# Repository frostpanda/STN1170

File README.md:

<h2><b>Prototype of common OBD diagnostic board </b></h2>

Device uses STN1170 chip in QFTP package, form ScanTool company and it is compatible with ELM327, based on information, which can be found in datasheet about this integrated circuit. 

Main assumption about this prototype to be a modular to lower the cost of the device, because only 3 samples can be acquired through ScanTool company, so prototype has two boards. One with STN1170 and necessary components and second one with transceivers, which are required for communication with proper protocols and OBD chip, but also contains wireless and wired communication. 

Wireless communication was planned RN4870 BLE module. But because of bad implementation (???) or module was broken I can not force him to work properly. In the end it lost MAC address and this is common for modules, based on IS187x Bluetooth LE ICs and the main reason for it was as Microchip support claim “Inappropriate module reset”, but I didn’t get answer for my question, when I asked about, how this module should be reset, to prevent such behavior in the future. Finally I decided for HM-13 module. Module is already implemented and I need to do more tweaking in revision 2 to push next revision. For now module is working on revision 1 prototype board.

Wired communication with PC uses CP2102N UART to Bridge ICs. His cost is lower than FTDI chips and has a lot possible ways to configure it, beginning from drivers, ending at ICs, but soldering it without hot air station is not easy task to do, but it can be done with some patience.

After success of 1st prototype (working!), second was made. On the 2nd prototype everything was moved to the one 2 layers PCB board, with dimension of 4cm x 6cm (I will try to make it even smaller!, but I am concern about EMC problem with it and this could require use 4 layer PCB). Some of components are on the bottom side of the board. 

Checked protocols:
- [x] High Speed CAN
- [x] Medium Speed CAN 
- [x] Single Wire CAN 
- [x] K-LINE
- [x] L-LINE
- [ ] VPW 
- [ ] PWM

Basic connection tested with:
- Fiat Punto MK2 1.2 8V (MultiEcuScan)
- Opel Vectra C 1.8 16V 122KM 
- Citroen DS4 
- Mazda 3 BK 1.6 105KM Z6 2008 (ForScan)

Gallery: https://imgur.com/a/UtiDV

Video: https://youtu.be/GFeOGx49xKc

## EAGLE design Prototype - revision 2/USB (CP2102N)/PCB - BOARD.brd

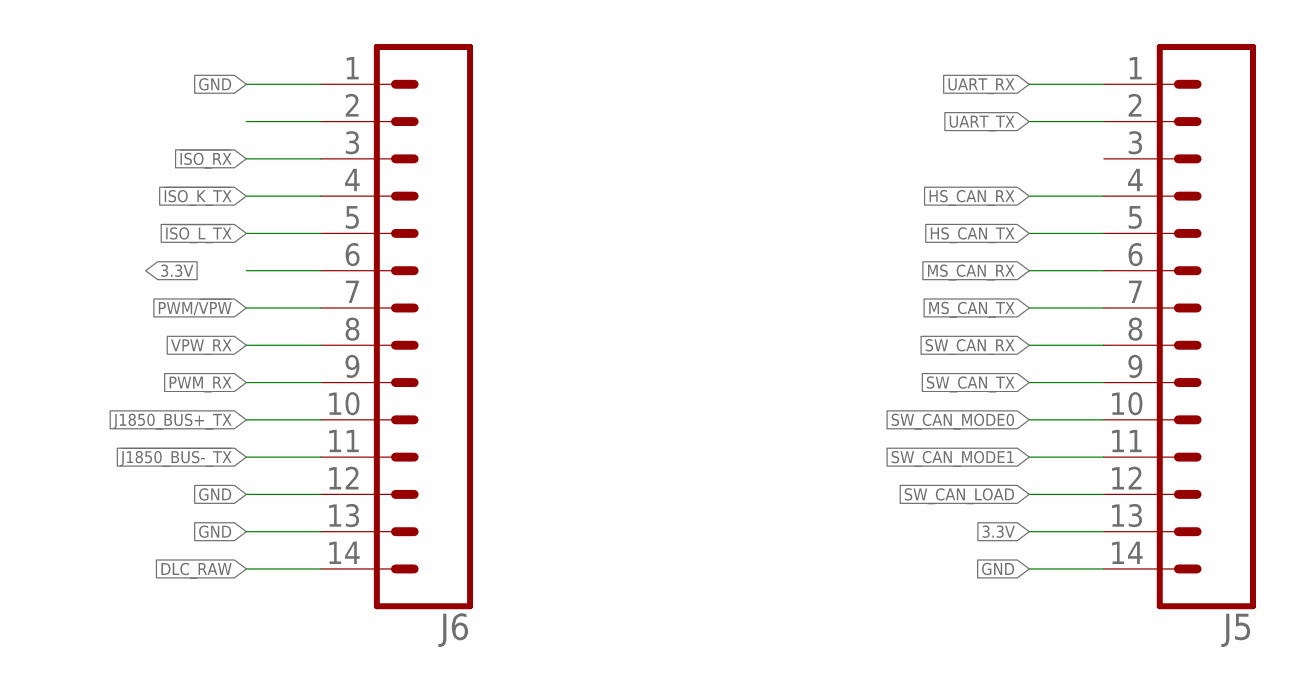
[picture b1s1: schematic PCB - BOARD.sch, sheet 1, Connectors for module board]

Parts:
J5, J6: CONN_14; 1X14

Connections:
3.3V: J5.13, J6.6; also elsewhere on the board
!ISO_K_TX: J6.4; also elsewhere on the board
!ISO_L_TX: J6.5; also elsewhere on the board
!ISO_RX: J6.3; also elsewhere on the board
!J1850_BUS-_TX: J6.11; also elsewhere on the board
DLC_RAW: J6.14; also elsewhere on the board
GND: J5.14, J6.1, J6.2, J6.12, J6.13; also elsewhere on the board
HS_CAN_RX: J5.4; also elsewhere on the board
HS_CAN_TX: J5.5; also elsewhere on the board
J1850_BUS+_TX: J6.10; also elsewhere on the board
MS_CAN_RX: J5.6; also elsewhere on the board
MS_CAN_TX: J5.7; also elsewhere on the board
PWM/!VPW: J6.7; also elsewhere on the board
PWM_RX: J6.9; also elsewhere on the board
SW_CAN_LOAD: J5.12; also elsewhere on the board
SW_CAN_MODE0: J5.10; also elsewhere on the board
SW_CAN_MODE1: J5.11; also elsewhere on the board
SW_CAN_RX: J5.8; also elsewhere on the board
SW_CAN_TX: J5.9; also elsewhere on the board
UART_RX: J5.1; also elsewhere on the board
UART_TX: J5.2; also elsewhere on the board
VPW_RX: J6.8; also elsewhere on the board

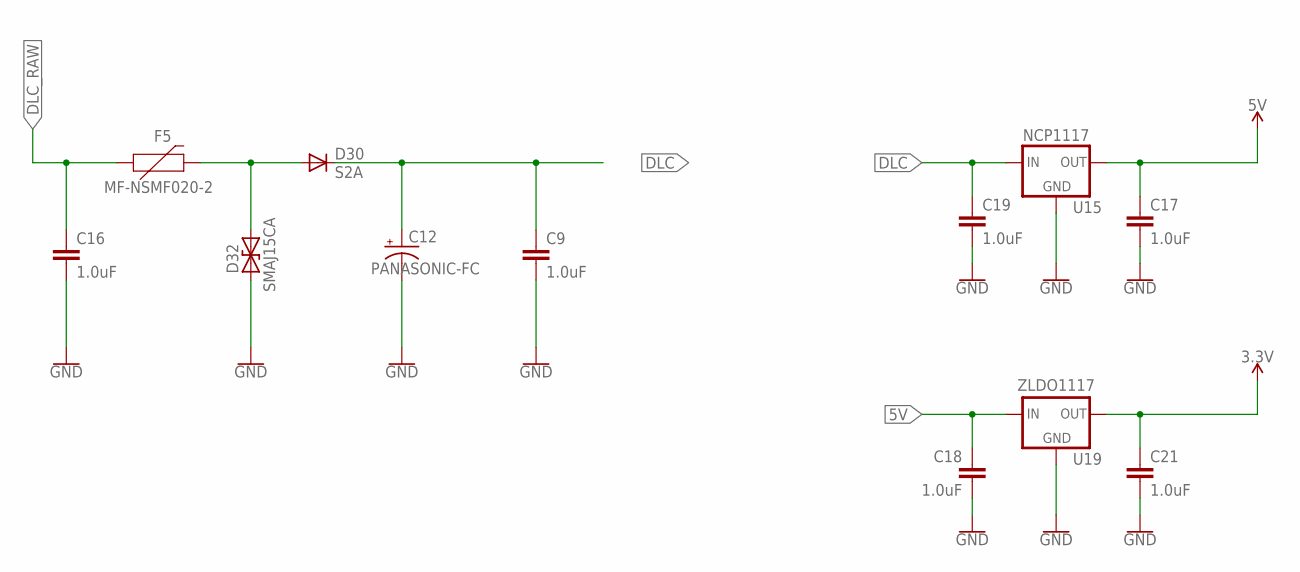
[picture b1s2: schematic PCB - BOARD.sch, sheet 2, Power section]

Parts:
C9, C16, C17, C18, C19, C21: 1.0uF; 0805
C12: PANASONIC-FC; 5X11
D30: S2A; DO214AA
D32: SMAJ15CA; DO214AC
F5: MF-NSMF020-2; 1206
U15: NCP1117; TO-252
U19: ZLDO1117; SOT223

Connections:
3.3V: C21.1, U19.2 (OUT), U19.4 (OUT); also elsewhere on the board
5V: C17.1, C18.1, U15.2 (OUT), U19.3 (IN); also elsewhere on the board
DLC: C9.1, C12.2 (+), C19.1, D30.C, U15.3 (IN); also elsewhere on the board
DLC_RAW: C16.1, F5.1; also elsewhere on the board
DLC_RAW2: D30.A, D32.C (2), F5.2
GND: C9.2, C12.1 (-), C16.2, C17.2, C18.2, C19.2, C21.2, D32.A (1), U15.1 (GND), U19.1 (GND); also elsewhere on the board

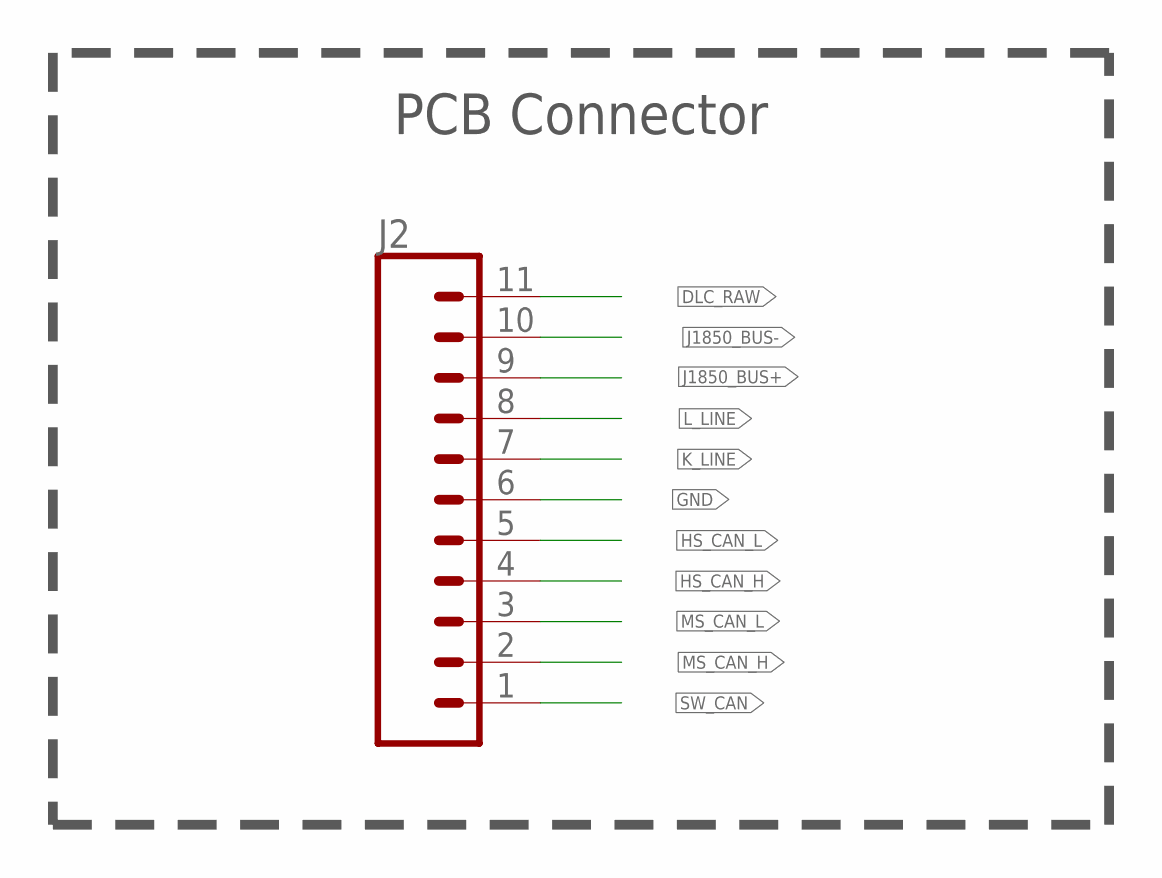
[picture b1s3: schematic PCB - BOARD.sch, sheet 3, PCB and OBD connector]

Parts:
J2: CONN_11; 1X11

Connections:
DLC_RAW: J2.11; also elsewhere on the board
GND: J2.6; also elsewhere on the board
HS_CAN_H: J2.4; also elsewhere on the board
HS_CAN_L: J2.5; also elsewhere on the board
J1850_BUS+: J2.9; also elsewhere on the board
J1850_BUS-: J2.10; also elsewhere on the board
K_LINE: J2.7; also elsewhere on the board
L_LINE: J2.8; also elsewhere on the board
MS_CAN_H: J2.2; also elsewhere on the board
MS_CAN_L: J2.3; also elsewhere on the board
SW_CAN: J2.1; also elsewhere on the board

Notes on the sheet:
PCB Connector

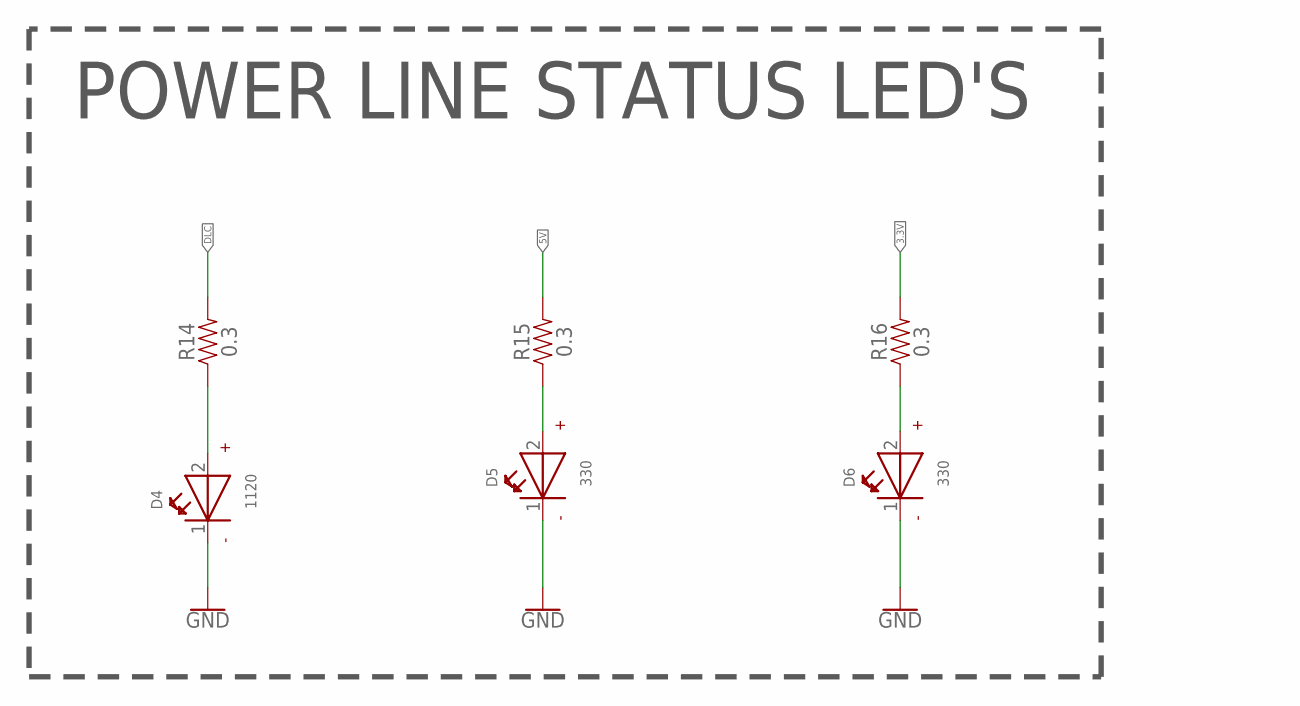
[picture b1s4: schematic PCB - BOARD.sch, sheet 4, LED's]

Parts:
D4: 1120; WL-SMCW_1206
D5, D6: 330; WL-SMCW_1206
R14, R15, R16: 0.3; 0805

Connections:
3.3V: R16.2; also elsewhere on the board
5V: R15.2; also elsewhere on the board
DLC: R14.2; also elsewhere on the board
GND: D4.1 (-), D5.1 (-), D6.1 (-); also elsewhere on the board
unnamed: D6.2 (+), R16.1
unnamed: D5.2 (+), R15.1
unnamed: D4.2 (+), R14.1

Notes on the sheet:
POWER LINE STATUS LED'S

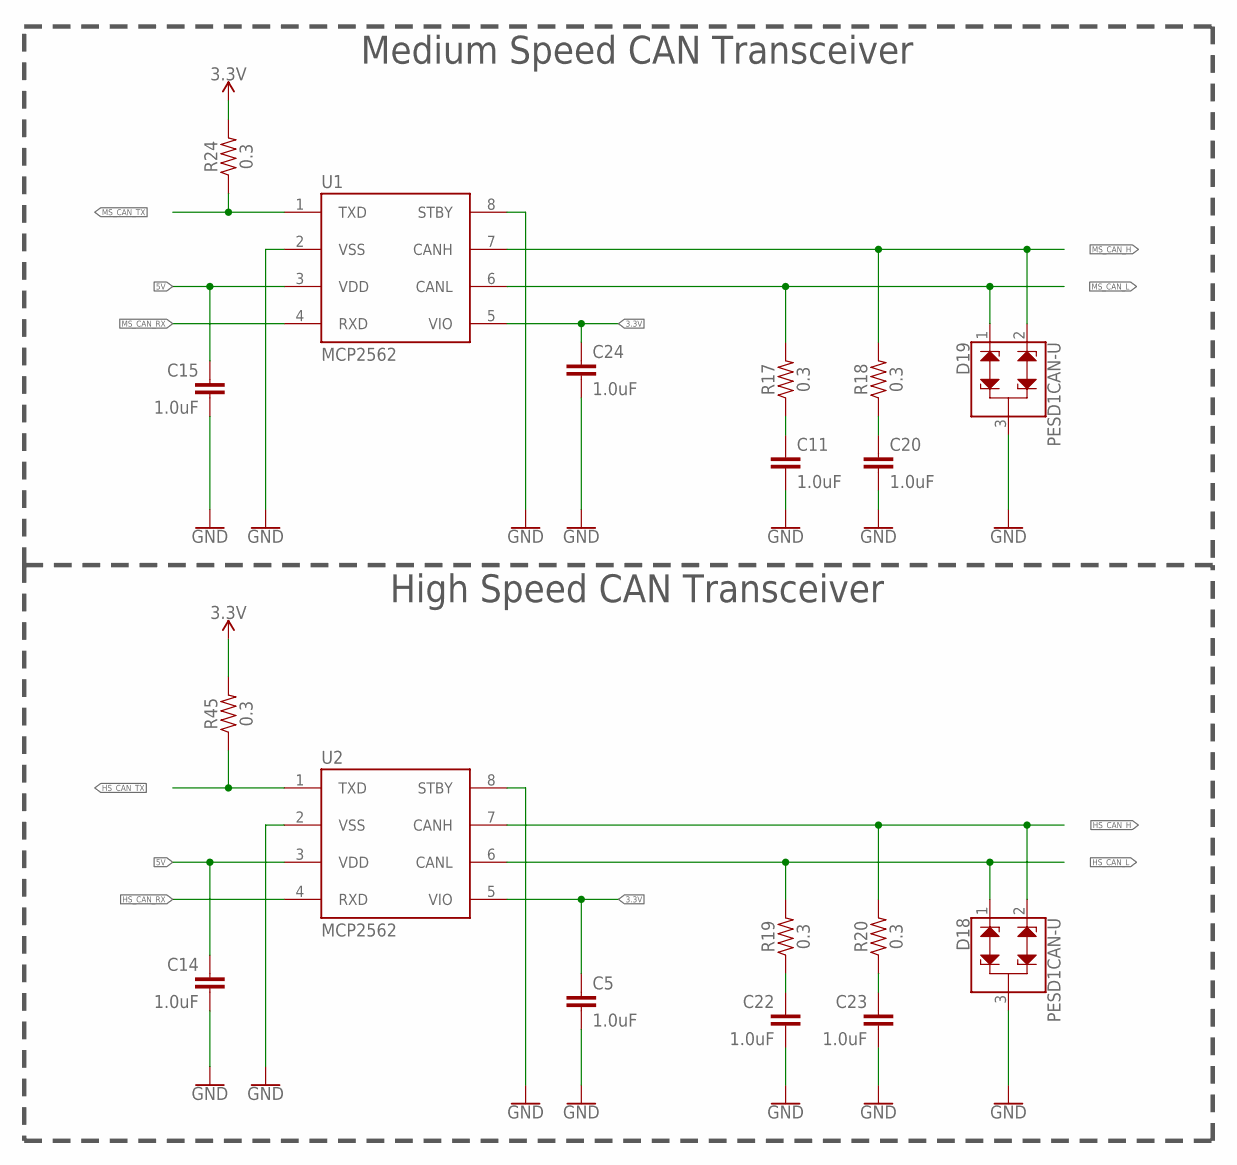
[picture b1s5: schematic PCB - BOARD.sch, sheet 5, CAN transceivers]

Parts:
C5, C11, C14, C15, C20, C22, C23, C24: 1.0uF; 0805
D18, D19: PESD1CAN-U; SOT323
R17, R18, R19, R20, R24, R45: 0.3; 0805
U1, U2: MCP2562; SOIC-8

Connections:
3.3V: C5.1, C24.1, R24.2, R45.2, U1.5 (VIO), U2.5 (VIO); also elsewhere on the board
5V: C14.1, C15.1, U1.3 (VDD), U2.3 (VDD); also elsewhere on the board
GND: C5.2, C11.2, C14.2, C15.2, C20.2, C22.2, C23.2, C24.2, D18.3, D19.3, U1.2 (VSS), U1.8 (STBY), U2.2 (VSS), U2.8 (STBY); also elsewhere on the board
HS_CAN_H: D18.2, R20.2, U2.7 (CANH); also elsewhere on the board
HS_CAN_L: D18.1, R19.2, U2.6 (CANL); also elsewhere on the board
HS_CAN_RX: U2.4 (RXD); also elsewhere on the board
HS_CAN_TX: R45.1, U2.1 (TXD); also elsewhere on the board
MS_CAN_H: D19.2, R18.2, U1.7 (CANH); also elsewhere on the board
MS_CAN_L: D19.1, R17.2, U1.6 (CANL); also elsewhere on the board
MS_CAN_RX: U1.4 (RXD); also elsewhere on the board
MS_CAN_TX: R24.1, U1.1 (TXD); also elsewhere on the board
unnamed: C11.1, R17.1
unnamed: C20.1, R18.1
unnamed: C22.1, R19.1
unnamed: C23.1, R20.1

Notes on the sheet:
Medium Speed CAN Transceiver
High Speed CAN Transceiver

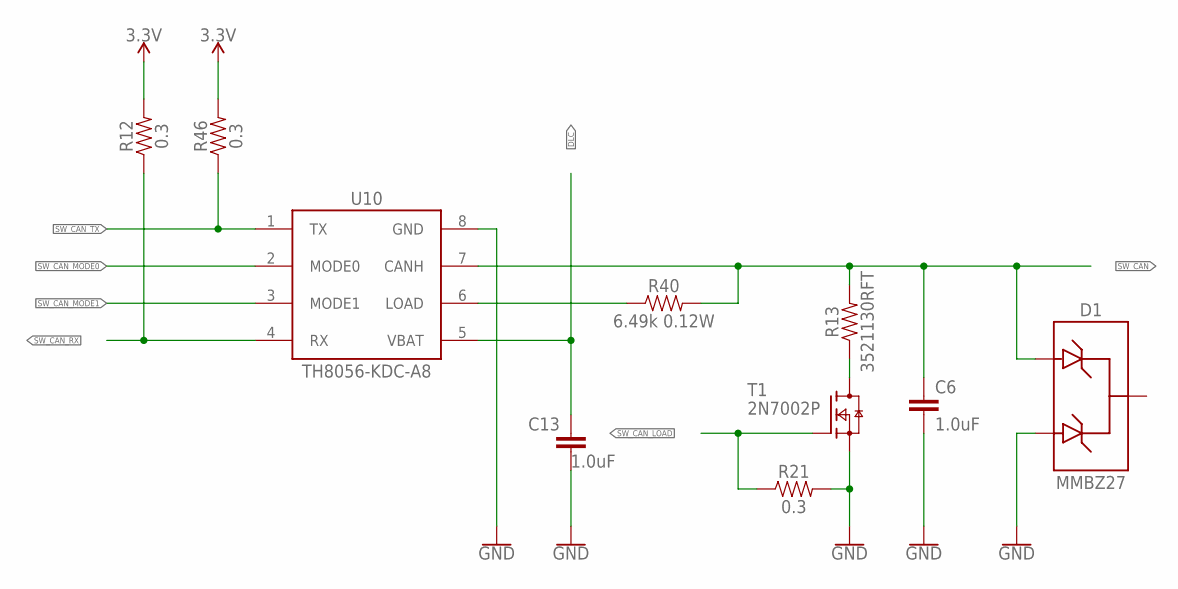
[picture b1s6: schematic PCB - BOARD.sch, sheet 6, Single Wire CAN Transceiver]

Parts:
C6, C13: 1.0uF; 0805
D1: MMBZ27; SOT23-3
R12, R21, R46: 0.3; 0805
R13: 3521130RFT; 3521
R40: 6.49k 0.12W; 1206
T1: 2N7002P; SOT23
U10: TH8056-KDC-A8; SOIC-8

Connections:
3.3V: R12.2, R46.2; also elsewhere on the board
DLC: C13.1, U10.5 (VBAT); also elsewhere on the board
GND: C6.2, C13.2, D1.2 (A2), R21.2, T1.2 (S), U10.8 (GND); also elsewhere on the board
LOAD: R40.1, U10.6 (LOAD)
unnamed: R13.1, T1.3 (D)
SW_CAN: C6.1, D1.1 (A1), R13.2, R40.2, U10.7 (CANH); also elsewhere on the board
SW_CAN_LOAD: R21.1, T1.1 (G); also elsewhere on the board
SW_CAN_MODE0: U10.2 (MODE0); also elsewhere on the board
SW_CAN_MODE1: U10.3 (MODE1); also elsewhere on the board
SW_CAN_RX: R12.1, U10.4 (RX); also elsewhere on the board
SW_CAN_TX: R46.1, U10.1 (TX); also elsewhere on the board

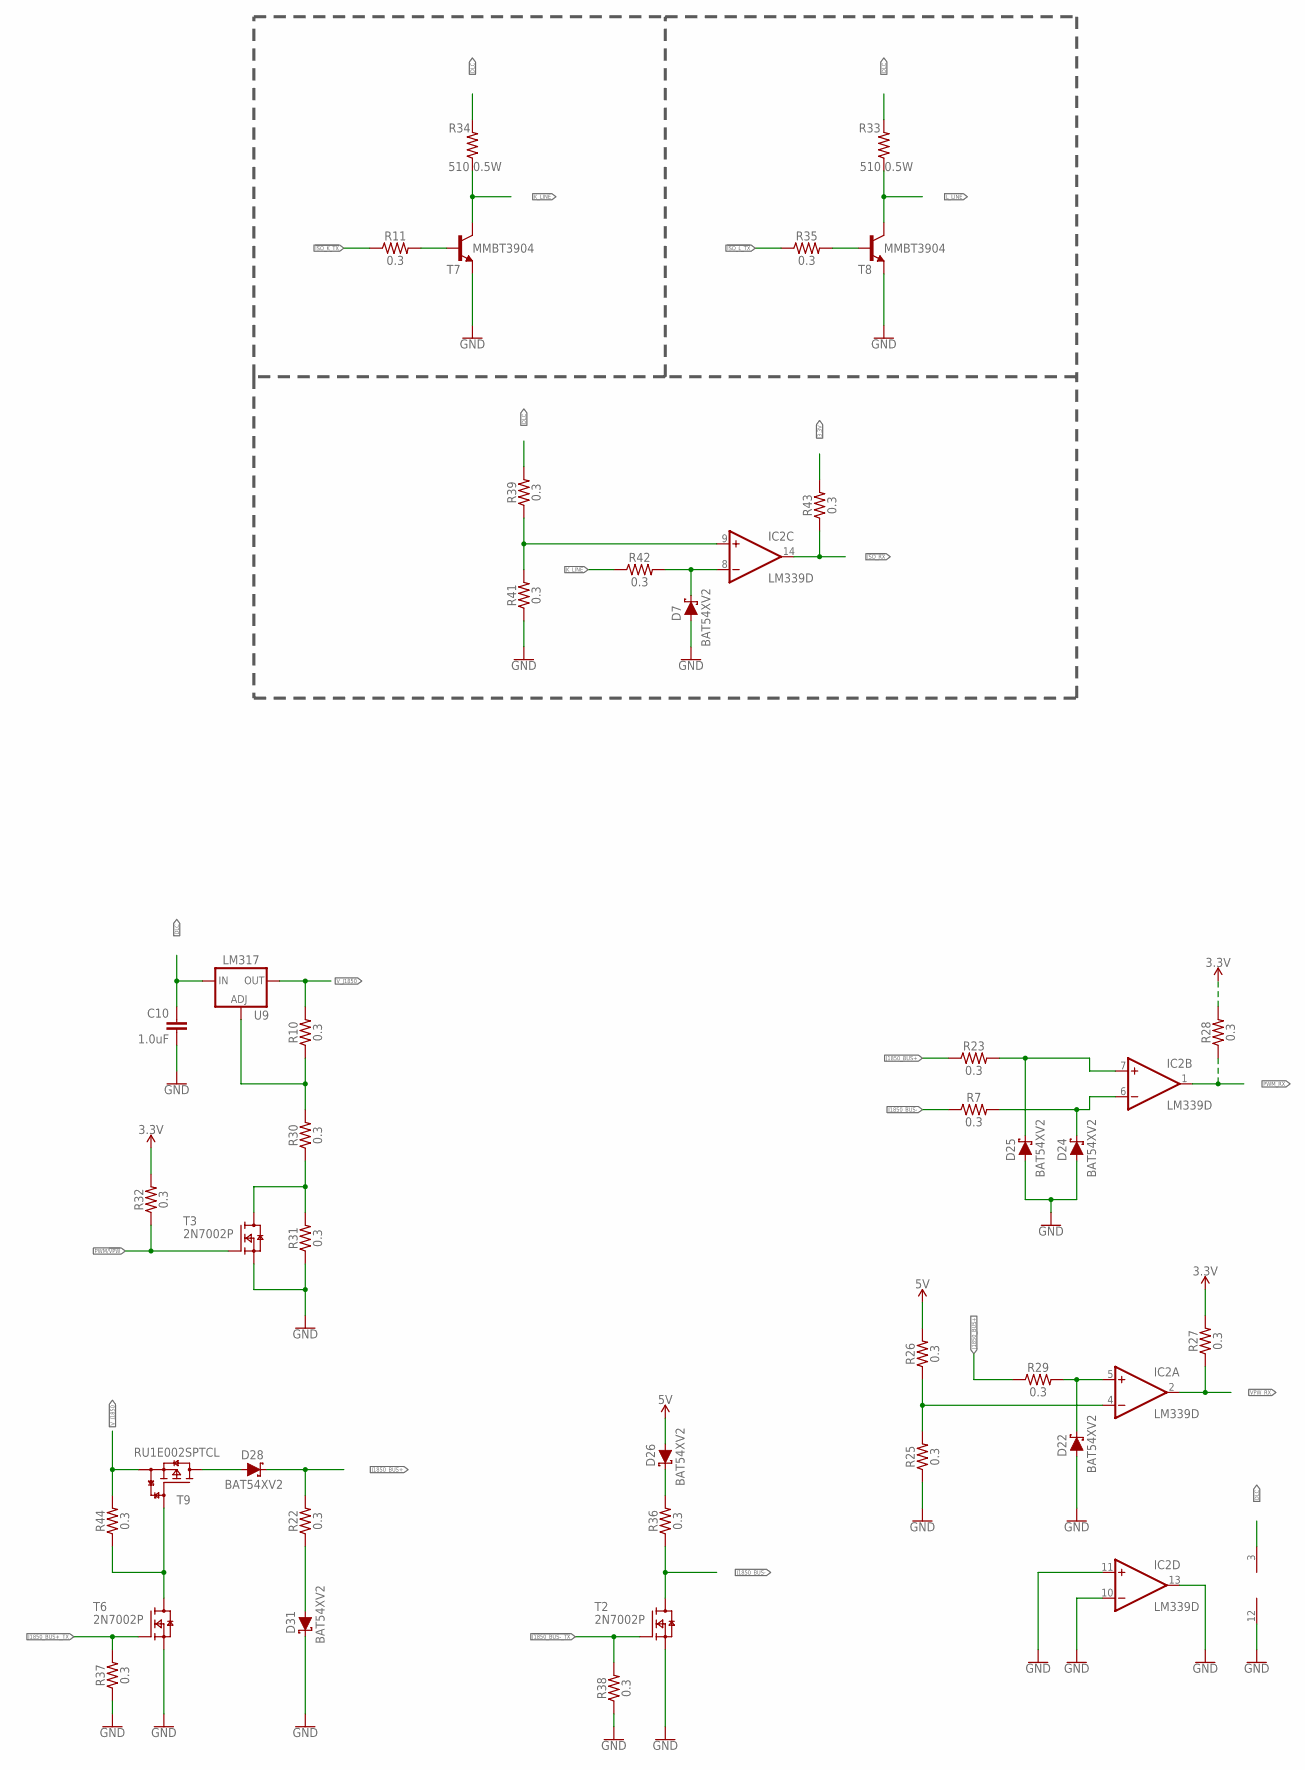
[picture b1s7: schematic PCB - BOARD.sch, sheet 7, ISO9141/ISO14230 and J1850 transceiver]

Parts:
C10: 1.0uF; 0805
D7, D22, D24, D25, D26, D28, D31: BAT54XV2; SOD-523F
IC2: LM339D; SO14
R7, R10, R11, R22, R23, R25, R26, R27, R28, R29, R30, R31, R32, R35, R36, R37, R38, R39, R41, R42, R43, R44: 0.3; 0805
R33, R34: 510 0.5W; 1210
T2, T3, T6: 2N7002P; SOT23
T7, T8: MMBT3904; SOT23-BEC
T9: RU1E002SPTCL; SOT323
U9: LM317; SOT223

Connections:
3.3V: R27.2, R28.2, R32.2, R43.2; also elsewhere on the board
5V: D26.A, R26.2; also elsewhere on the board
!ISO_K_TX: R11.1; also elsewhere on the board
!ISO_L_TX: R35.1; also elsewhere on the board
!ISO_RX: IC2.14 (OUT), R43.1; also elsewhere on the board
!J1850_BUS-_TX: R38.2, T2.1 (G); also elsewhere on the board
ADJ: R10.1, R30.2, U9.1 (ADJ)
COMPARATOR+: D22.C, IC2.5 (+IN), R29.2
COMPARATOR-: IC2.4 (-IN), R25.2, R26.1
DLC: C10.1, IC2.3 (V+), R33.2, R34.2, R39.2, U9.3 (IN); also elsewhere on the board
GND: C10.2, D7.A, D22.A, D24.A, D25.A, D31.C, IC2.10 (-IN), IC2.11 (+IN), IC2.12 (GND), IC2.13 (OUT), R25.1, R31.1, R37.1, R38.1, R41.1, T2.2 (S), T3.2 (S), T6.2 (S), T7.E, T8.E; also elsewhere on the board
J1850_BUS+: D25.C, D28.C, IC2.7 (+IN), R22.2, R23.1, R23.2, R29.1; also elsewhere on the board
J1850_BUS+_TX: R37.2, T6.1 (G); also elsewhere on the board
J1850_BUS-: D24.C, IC2.6 (-IN), R7.1, R7.2, R36.1, T2.3 (D); also elsewhere on the board
K-LINE: D7.C, IC2.8 (-IN), R42.2
K_LINE: R34.1, R42.1, T7.C; also elsewhere on the board
L_LINE: R33.1, T8.C; also elsewhere on the board
unnamed: R44.1, T6.3 (D), T9.1 (G)
unnamed: D26.C, R36.2
unnamed: IC2.9 (+IN), R39.1, R41.2
unnamed: D28.A, T9.3 (D)
unnamed: D31.A, R22.1
unnamed: R35.2, T8.B
unnamed: R11.2, T7.B
unnamed: R30.1, R31.2, T3.3 (D)
PWM/!VPW: R32.1, T3.1 (G); also elsewhere on the board
PWM_RX: IC2.1 (OUT), R28.1; also elsewhere on the board
VPW_RX: IC2.2 (OUT), R27.1; also elsewhere on the board
V_J1850: R10.2, R44.2, T9.2 (S), U9.2 (OUT), U9.4 (OUT)

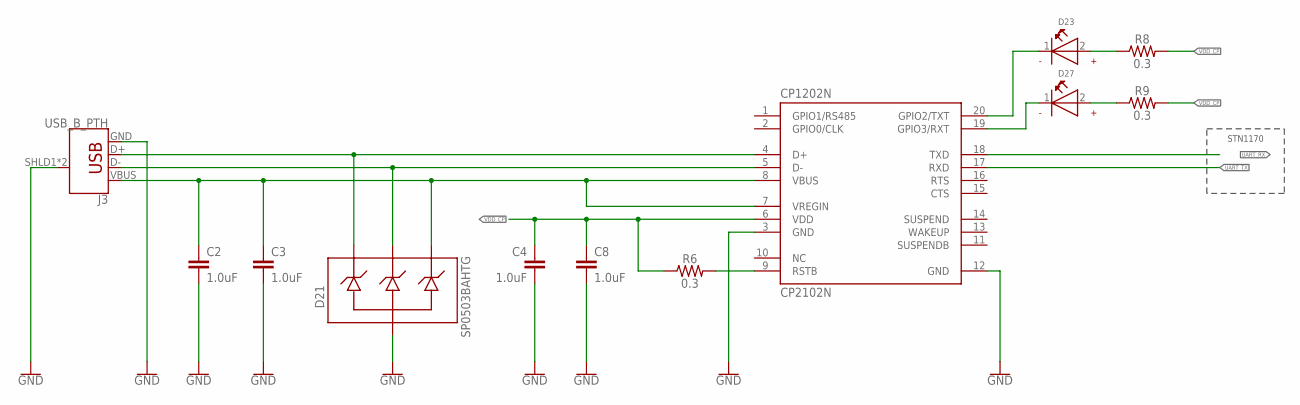
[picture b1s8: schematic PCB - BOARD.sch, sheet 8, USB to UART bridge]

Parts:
C2, C3, C4, C8: 1.0uF; 0805
CP1202N: CP2102N; QFN20
D21: SP0503BAHTG; SOT143-4
D23, D27: WL-SMCW-150120BS75000-B; WL-SMCW_1206
J3: USB_B_PTH; USB-B-PTH
R6, R8, R9: 0.3; 0805

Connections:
D+: CP1202N.4 (D+), D21.4, J3.D+
D-: CP1202N.5 (D-), D21.3, J3.D-
GND: C2.2, C3.2, C4.2, C8.2, CP1202N.3 (GND), CP1202N.12 (GND), D21.1, J3.GND, J3.SHLD1 (SHIELD), J3.SHLD2 (SHIELD); also elsewhere on the board
unnamed: CP1202N.9 (RSTB), R6.2
unnamed: CP1202N.20 (GPIO2/TXT), D23.1 (-)
unnamed: CP1202N.19 (GPIO3/RXT), D27.1 (-)
unnamed: D23.2 (+), R8.1
unnamed: D27.2 (+), R9.1
UART_RX: CP1202N.18 (TXD); also elsewhere on the board
UART_TX: CP1202N.17 (RXD); also elsewhere on the board
VBUS: C2.1, C3.1, CP1202N.7 (VREGIN), CP1202N.8 (VBUS), D21.2, J3.VBUS
VDD_CP: C4.1, C8.1, CP1202N.6 (VDD), R6.1, R8.2, R9.2

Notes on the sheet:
STN1170

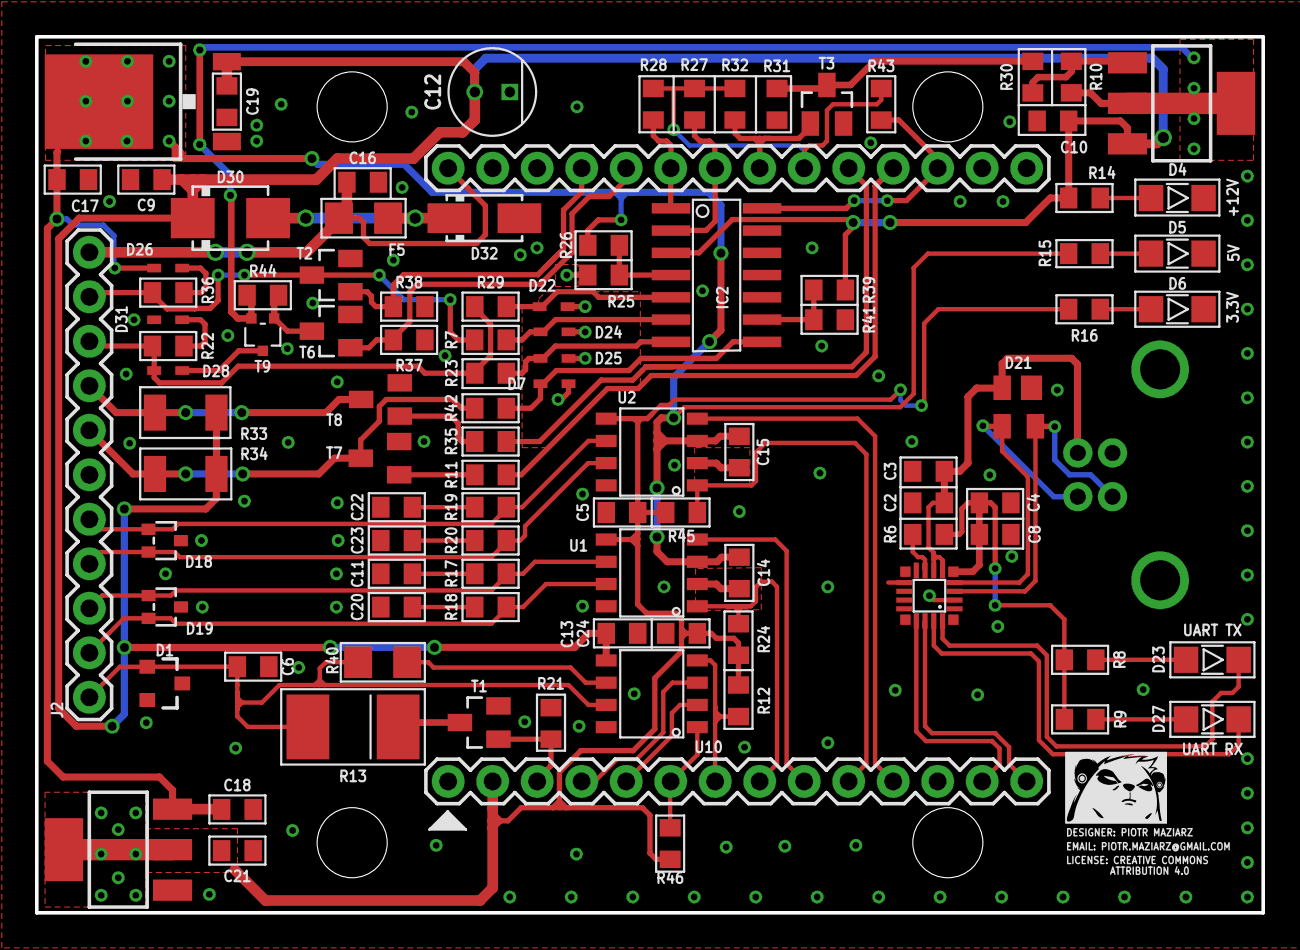
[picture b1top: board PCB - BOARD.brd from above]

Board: 2 copper layers, 70.0 x 50.0 mm, 103 parts (1 on the bottom side), 65 nets.

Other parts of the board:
U$1, U$2: LOGO2

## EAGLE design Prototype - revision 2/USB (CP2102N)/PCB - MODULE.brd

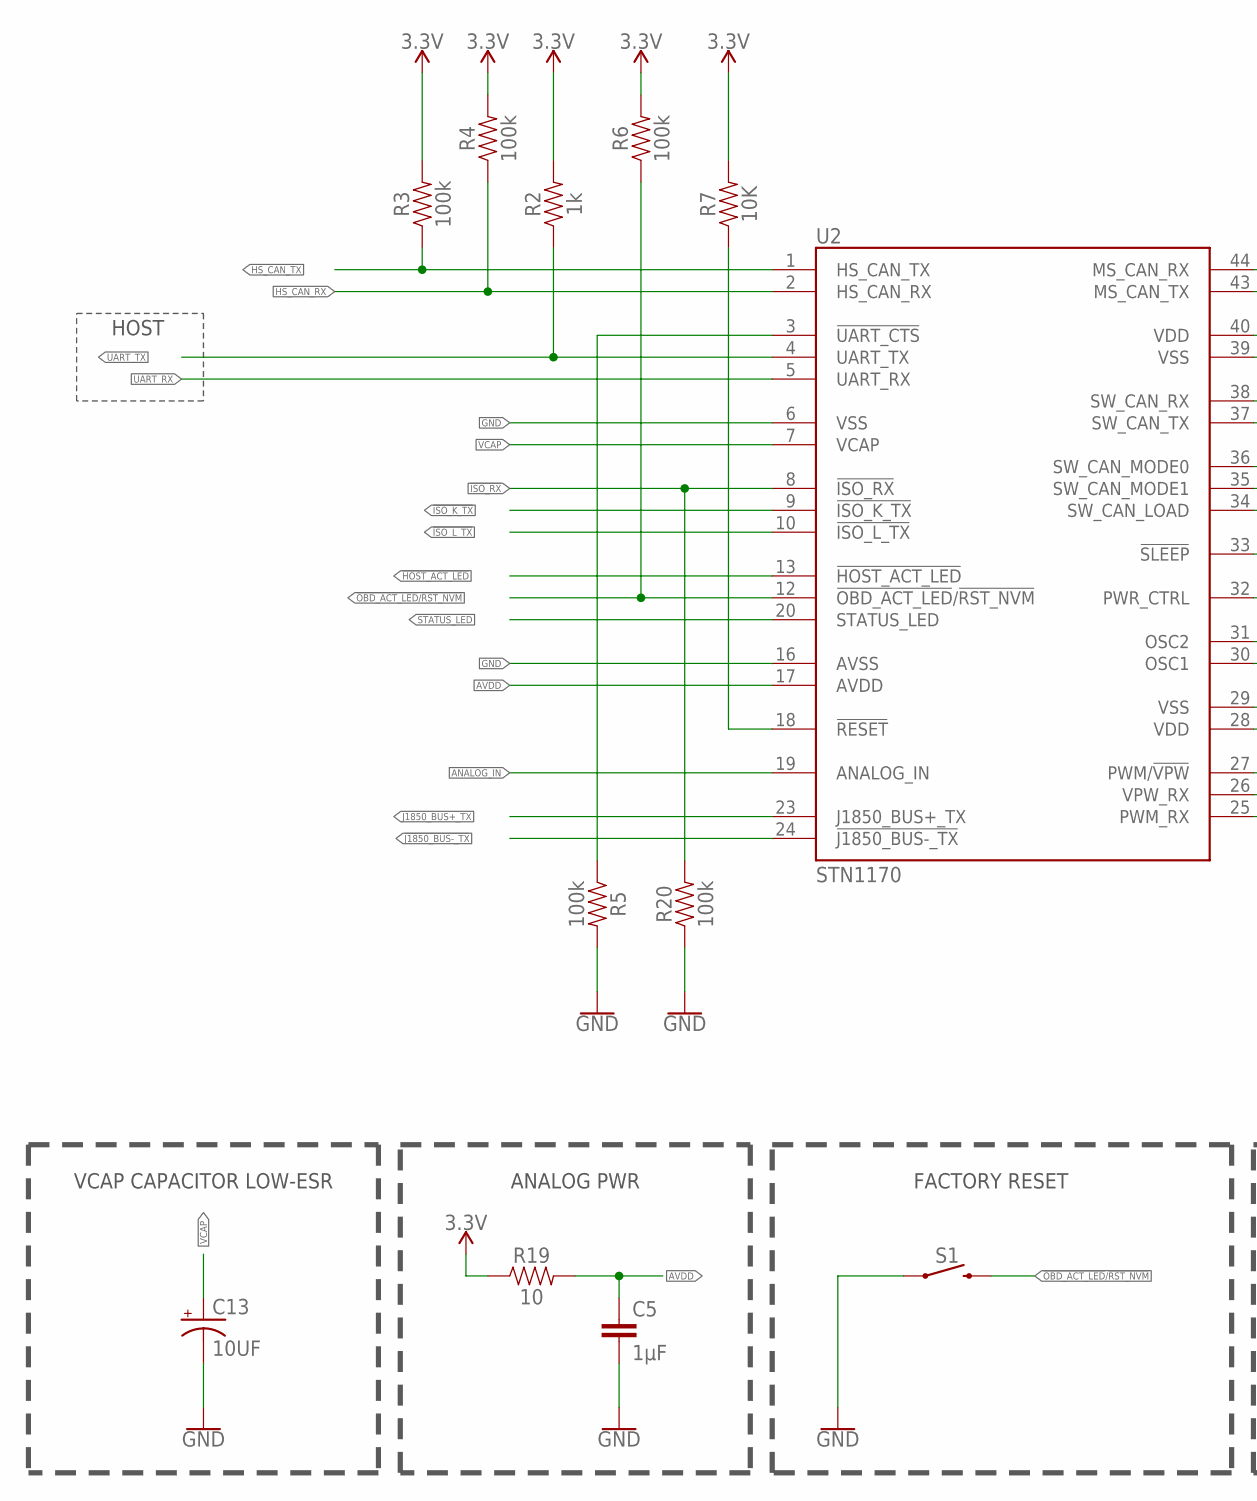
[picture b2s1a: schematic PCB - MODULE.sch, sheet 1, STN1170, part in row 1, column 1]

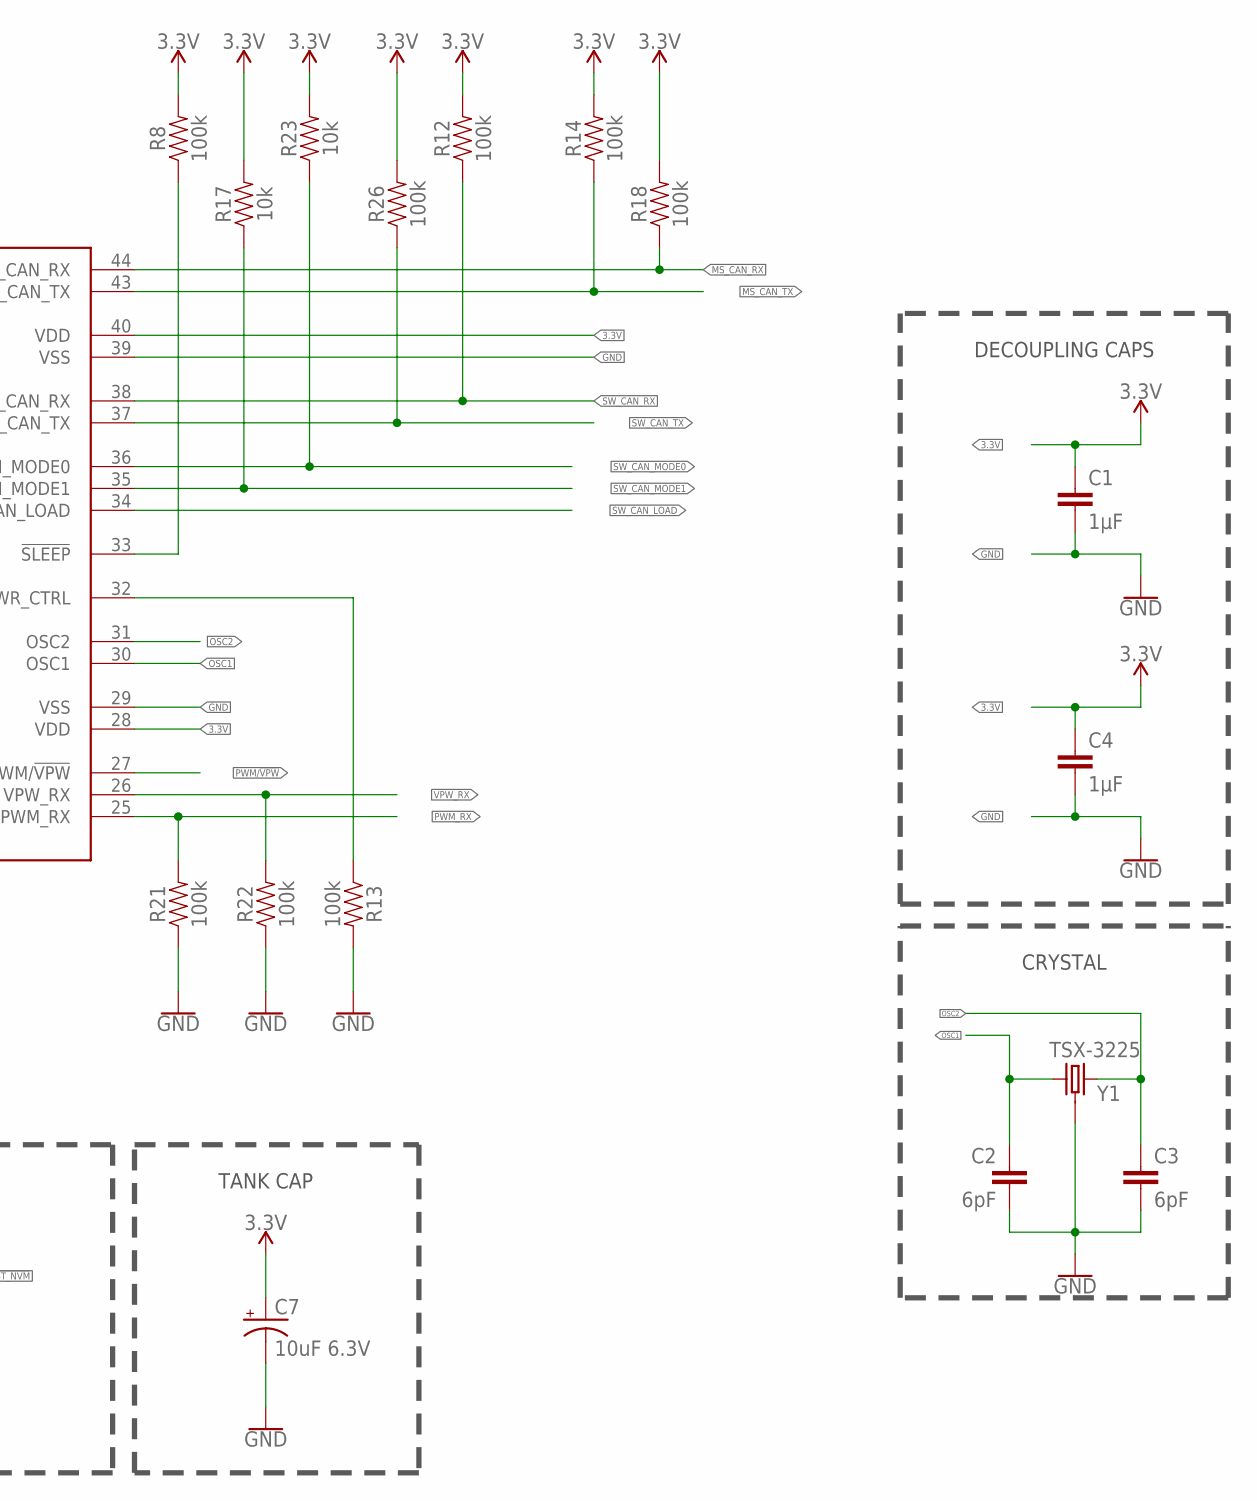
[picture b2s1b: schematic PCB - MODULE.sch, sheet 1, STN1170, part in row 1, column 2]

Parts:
C1, C4, C5: 1µF; 0805
C2, C3: 6pF; 0805
C7: 10uF 6.3V; EIA3216
C13: 10UF; 1206
R2: 1k; 0805
R3, R4, R5, R6, R8, R12, R13, R14, R18, R20, R21, R22, R26: 100k; 0805
R7: 10K; 0805
R17, R23: 10k; 0805
R19: 10; 0805
S1: B3U; B3U-WO-GT-WO-B
U2: STN1170; TQFP44
Y1: TSX-3225; TSX-3225-SOLDERING-IRON

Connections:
3.3V: C1.1, C4.1, C7.+, R2.2, R3.2, R4.2, R6.2, R7.2, R8.2, R12.2, R14.2, R17.2, R18.2, R19.1, R23.2, R26.2, U2.28 (VDD), U2.40 (VDD); also elsewhere on the board
!HOST_ACT_LED: U2.13 (!HOST_ACT_LED); also elsewhere on the board
!ISO_K_TX: U2.9 (!ISO_K_TX); also elsewhere on the board
!ISO_L_TX: U2.10 (!ISO_L_TX); also elsewhere on the board
!ISO_RX: R20.2, U2.8 (!ISO_RX); also elsewhere on the board
!J1850_BUS-_TX: U2.24 (!J1850_BUS-_TX); also elsewhere on the board
!OBD_ACT_LED!/!RST_NVM: R6.1, S1.2, U2.12 (!OBD_ACT_LED!/!RST_NVM); also elsewhere on the board
!RESET: R7.1, U2.18 (!RESET)
!SLEEP: R8.1, U2.33 (!SLEEP)
!UART_CTS: R5.1, U2.3 (!UART_CTS)
ANALOG_IN: U2.19 (ANALOG_IN); also elsewhere on the board
AVDD: C5.1, R19.2, U2.17 (AVDD)
GND: C1.2, C2.2, C3.2, C4.2, C5.2, C7.-, C13.2 (-), R5.2, R13.2, R20.1, R21.1, R22.1, S1.1, U2.6 (VSS), U2.16 (AVSS), U2.29 (VSS), U2.39 (VSS), Y1.2 (3), Y1.4 (3); also elsewhere on the board
HS_CAN_RX: R4.1, U2.2 (HS_CAN_RX); also elsewhere on the board
HS_CAN_TX: R3.1, U2.1 (HS_CAN_TX); also elsewhere on the board
J1850_BUS+_TX: U2.23 (J1850_BUS+_TX); also elsewhere on the board
MS_CAN_RX: R18.1, U2.44 (MS_CAN_RX); also elsewhere on the board
MS_CAN_TX: R14.1, U2.43 (MS_CAN_TX); also elsewhere on the board
OSC1: C2.1, U2.30 (OSC1), Y1.1
OSC2: C3.1, U2.31 (OSC2), Y1.3 (2)
PWM/!VPW: U2.27 (PWM/!VPW!); also elsewhere on the board
PWM_RX: R21.2, U2.25 (PWM_RX); also elsewhere on the board
PWR_CTRL: R13.1, U2.32 (PWR_CTRL)
STATUS_LED: U2.20 (STATUS_LED); also elsewhere on the board
SW_CAN_LOAD: U2.34 (SW_CAN_LOAD); also elsewhere on the board
SW_CAN_MODE0: R23.1, U2.36 (SW_CAN_MODE0); also elsewhere on the board
SW_CAN_MODE1: R17.1, U2.35 (SW_CAN_MODE1); also elsewhere on the board
SW_CAN_RX: R12.1, U2.38 (SW_CAN_RX); also elsewhere on the board
SW_CAN_TX: R26.1, U2.37 (SW_CAN_TX); also elsewhere on the board
UART_RX: U2.5 (UART_RX); also elsewhere on the board
UART_TX: R2.1, U2.4 (UART_TX); also elsewhere on the board
VCAP: C13.1 (+), U2.7 (VCAP)
VPW_RX: R22.2, U2.26 (VPW_RX); also elsewhere on the board

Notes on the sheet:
HOST
ANALOG PWR
CRYSTAL
VCAP CAPACITOR LOW-ESR
DECOUPLING CAPS
FACTORY RESET
TANK CAP

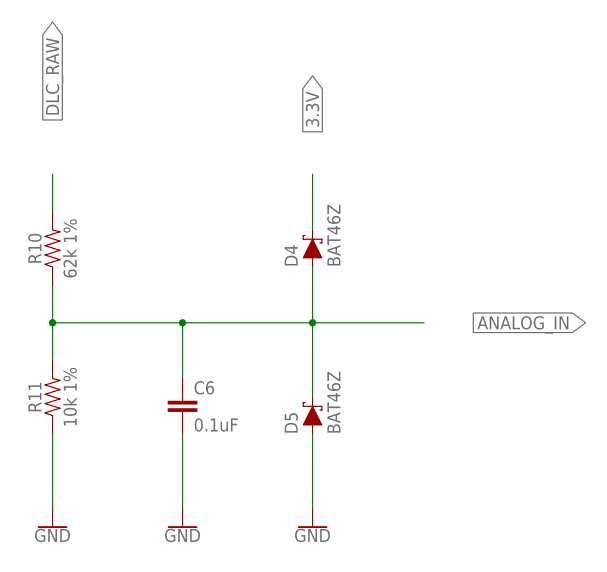
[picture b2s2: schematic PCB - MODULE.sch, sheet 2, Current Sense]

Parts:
C6: 0.1uF; 0805
D4, D5: BAT46Z; SOD-123
R10: 62k 1%; 0805
R11: 10k 1%; 0805

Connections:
3.3V: D4.C; also elsewhere on the board
ANALOG_IN: C6.1, D4.A, D5.C, R10.1, R11.2; also elsewhere on the board
DLC_RAW: R10.2; also elsewhere on the board
GND: C6.2, D5.A, R11.1; also elsewhere on the board

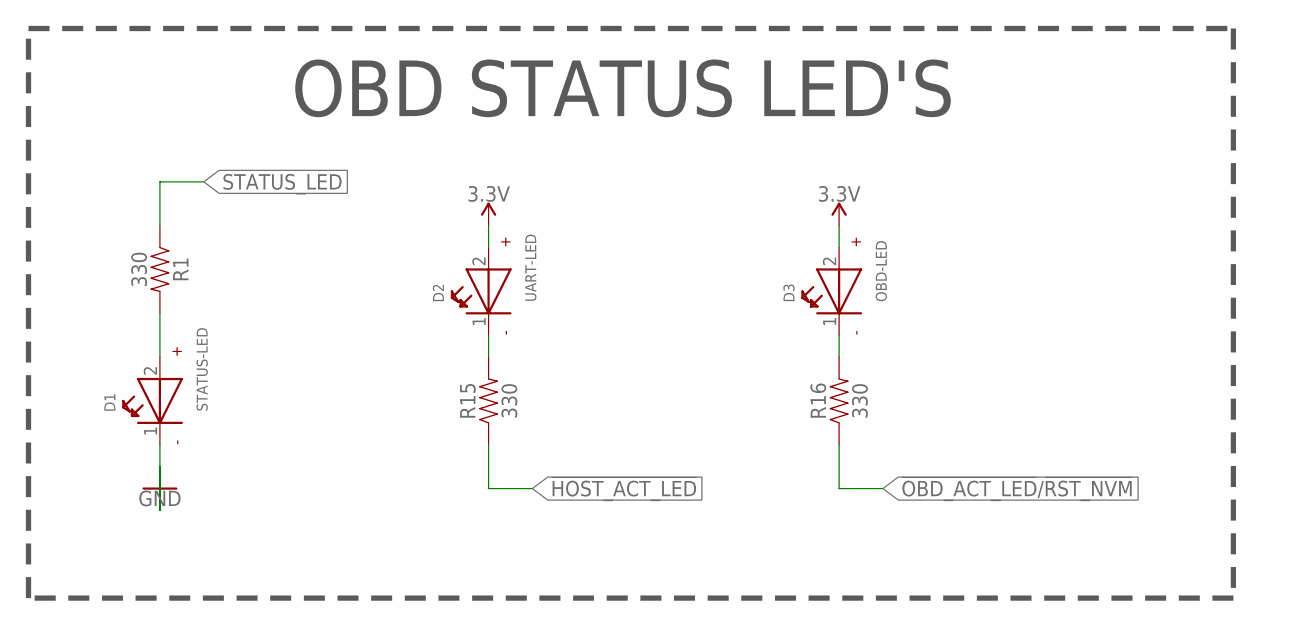
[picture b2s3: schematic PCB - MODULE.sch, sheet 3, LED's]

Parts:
D1: STATUS-LED; WL-SMCW_1206
D2: UART-LED; WL-SMCW_1206
D3: OBD-LED; WL-SMCW_1206
R1, R15, R16: 330; 0805

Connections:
3.3V: D2.2 (+), D3.2 (+); also elsewhere on the board
!HOST_ACT_LED: R15.1; also elsewhere on the board
!OBD_ACT_LED!/!RST_NVM: R16.1; also elsewhere on the board
GND: D1.1 (-); also elsewhere on the board
unnamed: D1.2 (+), R1.2
unnamed: D3.1 (-), R16.2
unnamed: D2.1 (-), R15.2
STATUS_LED: R1.1; also elsewhere on the board

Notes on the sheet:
OBD STATUS LED'S

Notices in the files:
Prototype - revision 2/USB (CP2102N)/PCB - BOARD.brd:
LICENSE: CREATIVE COMMONS
ATTRIBUTION 4.0
Prototype - revision 2/USB (CP2102N)/PCB - MODULE.brd:
CREATIVE COMMONS ATTRIBUTION 4.0
parts and their libraries:
SparkFun-Aesthetics: Licensing: Creative Commons ShareAlike 4.0 International - https://creativecommons.org/licenses/by-sa/4.0
EAGLE-COLOR_LED-rev17b: Copyright: Würth Elektronik
